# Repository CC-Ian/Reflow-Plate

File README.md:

# Reflow Plate
Yet another PCB Hotplate. Loosely inspired by the [AfterEarthLTD](https://github.com/AfterEarthLTD/Solder-Reflow-Plate) one.

Goals:
- 24V input voltage
- 2.5A Heater Current
- Type C PD and DC Barrel supported

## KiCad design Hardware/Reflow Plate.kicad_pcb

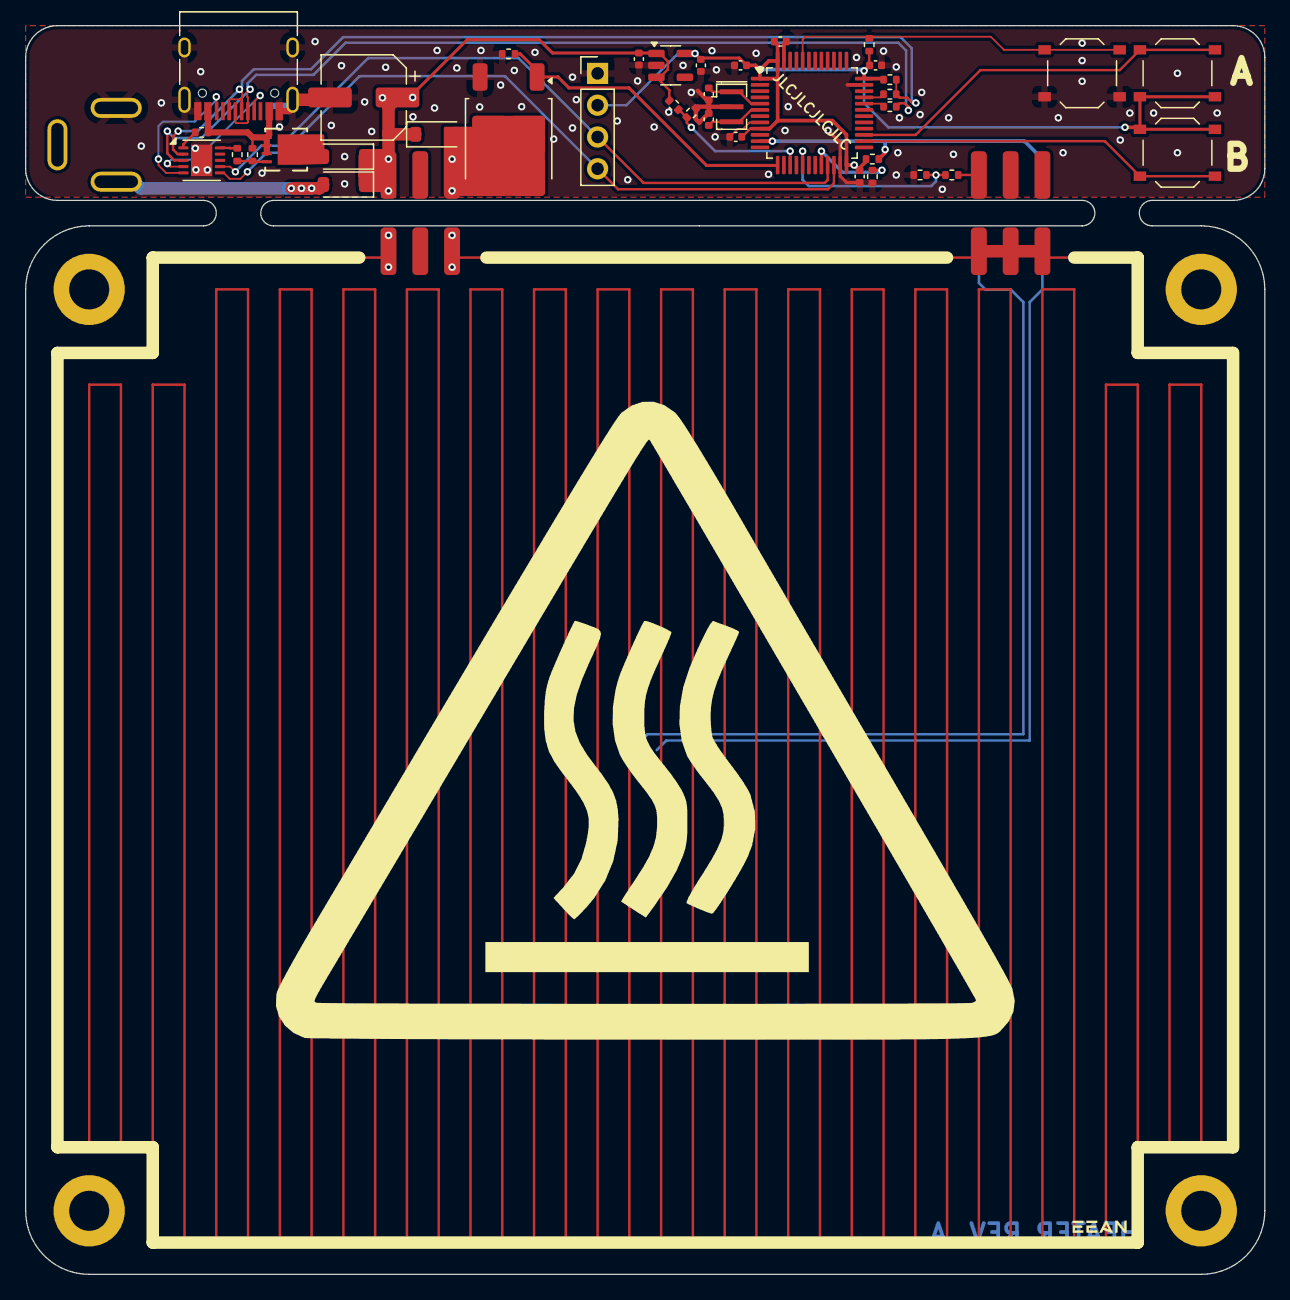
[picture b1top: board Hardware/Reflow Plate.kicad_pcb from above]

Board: 2 copper layers, 99.1 x 99.8 mm, 44 parts (1 on the bottom side), 32 nets.

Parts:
C1, C2: 1u; C_0402_1005Metric
C4: 220u; CP_Elec_6.3x7.7
C5, C6: 10p; C_0402_1005Metric
C7, C8, C9, C10, C11: 100n; C_0402_1005Metric
D1, D2: SS34; D_SOD-123
D3: D_Zener; D_SOD-123
J1: Barrel_Jack_MountingPin; DC Barrel
J2: 31-M-12; USB_C_Receptacle_HRO_TYPE-C-31-M-12
J3, J4, J5, J6: Conn_02x03_Odd_Even; 02x03
J7: Conn_01x04_Pin; PinHeader_1x04_P2.54mm_Vertical
MOSFET1: AONR21307; DFN8_3x3_EP_AOS
Q2: Q_NMOS_GDS; TO-252-2
R1, R5, R6: 10k; R_0402_1005Metric
R2, R4, R7, R12, R14: 100k; R_0402_1005Metric
R3: 10r; R_0402_1005Metric
R9, R10: 22; R_0402_1005Metric
R11: R; R_0402_1005Metric
R13, R15: 11k; R_0402_1005Metric
SW2, SW3, SW4: SW_Push; SW_Push_1P1T_XKB_TS-1187A
TH1: Thermistor_NTC; R_0805_2012Metric
U1: HUSB238; DFN-10-1EP_3x3mm_P0.5mm_EP1.7x2.5mm
U2: TLV73333PDBV; SOT-23-5
U3: STM32F103CBTx; LQFP-48_7x7mm_P0.5mm
Y1: 8M; Resonator_SMD_Murata_CSTxExxV-3Pin_3.0x1.1mm

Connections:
+3V3: C2.1, C7.1, C8.1, C9.1, C10.1, C11.1, J7.2, R6.1, R7.1, R11.2, SW3.1, SW4.1, U2.5 (OUT), U3.1 (VBAT), U3.9 (VDDA), U3.24 (VDD), U3.36 (VDD), U3.48 (VDD)
/HeatMon: J6.1, J6.3, J6.5, R14.1
/Heater: J3.1, J3.2, J3.5, J3.6, J4.1, J4.3, J4.5
BOOT0: R6.2, SW2.1, U3.44 (BOOT0)
BTN_A: SW3.2, U3.27 (PB14)
BTN_B: SW4.2, U3.26 (PB13)
GND: C1.2, C2.2, C4.2, C5.1, C6.1, C7.2, C8.2, C9.2, C10.2, C11.2, J1.2, J2.A1 (GND), J2.A12 (GND), J2.B1 (GND), J2.B12 (GND), J2.S1 (SHIELD), J6.6, J7.1, Q2.3 (S), R4.2, R5.1, R13.2, R15.2, SW2.2, U1.11 (GND), U2.2 (GND), U3.8 (VSSA), U3.23 (VSS), U3.35 (VSS), U3.47 (VSS), Y1.2
HeaterMeasure: R14.2, R15.1, U3.17 (PA7)
Heater_CTRL: Q2.1 (G), R4.1, U3.13 (PA3)
NTC_Measure: J6.2, R7.2, U3.11 (PA1)
unnamed: D1.2 (A), J1.1
unnamed: D2.2 (A), MOSFET1.5 (D), MOSFET1.6 (D), MOSFET1.7 (D), MOSFET1.8 (D)
unnamed: D3.2 (A), J5.1, J5.2, Q2.2 (D)
unnamed: J2.A5 (CC1), U1.4 (CC1)
unnamed: J2.B5 (CC2), U1.5 (CC2)
unnamed: J2.A4 (VBUS), J2.A9 (VBUS), J2.B4 (VBUS), J2.B9 (VBUS), MOSFET1.1 (S), MOSFET1.2 (S), MOSFET1.3 (S), R2.1, R3.1
unnamed: J4.2, TH1.2
unnamed: J4.6, TH1.1
unnamed: MOSFET1.4 (G), R1.2, R2.2
unnamed: R1.1, U1.10 (GATE)
unnamed: R3.2, U1.1 (VIN)
unnamed: R9.1, U3.32 (PA11)
unnamed: R10.1, U3.33 (PA12)
unnamed: R5.2, U3.20 (PB2)
unnamed: C5.2, U3.5 (PD0), Y1.1
unnamed: C6.2, U3.6 (PD1), Y1.3
SCL1: J7.3, U1.7 (SCL), U3.21 (PB10)
SDA1: J7.4, U1.6 (SDA), U3.22 (PB11)
USB_D+: J2.A6 (D+), J2.B6 (D+), R10.2, R11.1, U1.2 (D+)
USB_D-: J2.A7 (D-), J2.B7 (D-), R9.2, U1.3 (D-)
VBUS: C1.1, C4.1, D1.1 (K), D2.1 (K), D3.1 (K), J5.5, J5.6, R12.1, U2.1 (IN), U2.3 (EN)
VCCMeasure: R12.2, R13.1, U3.15 (PA5)

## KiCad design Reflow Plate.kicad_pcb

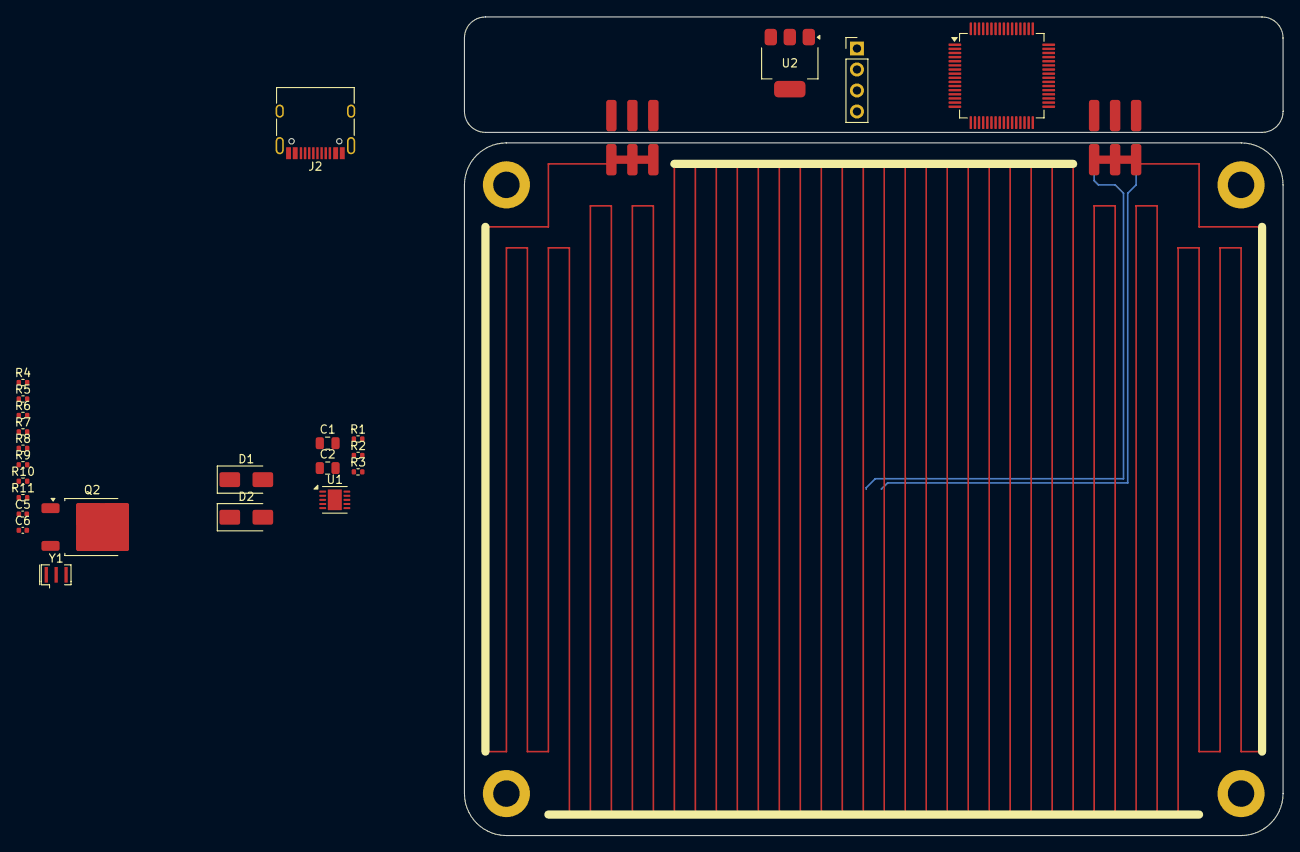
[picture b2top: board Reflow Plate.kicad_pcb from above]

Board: 2 copper layers, 99.1 x 99.1 mm, 29 parts (1 on the bottom side), 27 nets.

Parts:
C1, C2: 22u; C_0805_2012Metric
C5, C6: 10p; C_0402_1005Metric
D1, D2: SS34; D_SMA
J2: 31-M-12; USB_C_Receptacle_HRO_TYPE-C-31-M-12
J3, J4, J5, J6: Conn_02x03_Odd_Even; 02x03
J7: Conn_01x04_Pin; PinHeader_1x04_P2.54mm_Vertical
Q2: Q_NMOS_GDS; TO-252-2
R1, R5, R6, R8: 10k; R_0402_1005Metric
R2, R4, R7: 100k; R_0402_1005Metric
R3: 10r; R_0402_1005Metric
R9, R10: 22; R_0402_1005Metric
R11: R; R_0402_1005Metric
TH1: Thermistor_NTC; R_0805_2012Metric
U1: HUSB238; DFN-10-1EP_3x3mm_P0.5mm_EP1.7x2.5mm
U2: AMS1117-3.3; SOT-223-3_TabPin2
U4: STM32F103RBTx; LQFP-64_10x10mm_P0.5mm
Y1: 8M; Resonator_SMD_Murata_CSTxExxV-3Pin_3.0x1.1mm

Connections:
+3V3: C2.1, J7.2, R6.1, R7.1, R8.1, R11.2, U2.2 (VO), U4.13 (VDDA), U4.19 (VDD), U4.32 (VDD), U4.48 (VDD), U4.64 (VDD)
+24V: C1.1, D1.1 (K), D2.1 (K), J5.1, J5.3, J5.5, U2.3 (VI)
/Heater: J3.1, J3.3, J3.5, J4.1, J4.3, J4.5
BOOT0: R6.2, U4.60 (BOOT0)
GATE: R1.1, U1.10 (GATE)
GND: C1.2, C2.2, C5.1, C6.1, J2.A1 (GND), J2.A12 (GND), J2.B1 (GND), J2.B12 (GND), J2.S1 (SHIELD), J6.6, J7.1, Q2.3 (S), R4.2, R5.1, U1.11 (GND), U2.1 (GND), U4.12 (VSSA), U4.18 (VSS), U4.31 (VSS), U4.47 (VSS), U4.63 (VSS), Y1.2
Heater_CTRL: Q2.1 (G), R4.1, U4.62 (PB9)
NTC_Measure: J6.2, R7.2
unnamed: J2.A5 (CC1), U1.4 (CC1)
unnamed: J2.B5 (CC2), U1.5 (CC2)
unnamed: J2.A4 (VBUS), J2.A9 (VBUS), J2.B4 (VBUS), J2.B9 (VBUS), R2.2, R3.1
unnamed: J4.2, TH1.2
unnamed: J4.6, TH1.1
unnamed: J6.1, J6.3, J6.5, Q2.2 (D)
unnamed: R1.2, R2.1
unnamed: R3.2, U1.1 (VIN)
unnamed: R8.2, U4.7 (NRST)
unnamed: R9.1, U4.44 (PA11)
unnamed: R10.1, U4.45 (PA12)
unnamed: R5.2, U4.28 (PB2)
unnamed: C5.2, U4.5 (PD0), Y1.1
unnamed: C6.2, U4.6 (PD1), Y1.3
SCL1: J7.3, U1.7 (SCL), U4.58 (PB6)
SDA1: J7.4, U1.6 (SDA), U4.59 (PB7)
UDB_D+: J2.A6 (D+), J2.B6 (D+), U1.2 (D+)
UDB_D-: J2.A7 (D-), J2.B7 (D-), U1.3 (D-)
USB_D+: R10.2, R11.1

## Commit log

2024-03-27 Initial Layout
2024-03-27 Move to subdirectory
2024-03-27 Moved to siftware directory
2024-03-28 Add readme, bad power routing, final heater idea. Likely needs new layout.
2024-03-29 Closer to final placement of power components. Shooting for single sided assembly. Still some scuffed placements. Really packed. Missing likely needed ground planes.
2024-03-29 Final power layout. Changing LDO to SOT-23-5
2024-03-31 Ditch rev 1, moving on to rev 2.
2024-04-01 Rev 'b'. Having this produced. Added some voltage monitors. cleaned up traces. Moved i2c lines to i2c2. forgot to add pull-ups. the ones in the display should work though.
2024-04-20 Initial Prototype gerbers. Found problems.
